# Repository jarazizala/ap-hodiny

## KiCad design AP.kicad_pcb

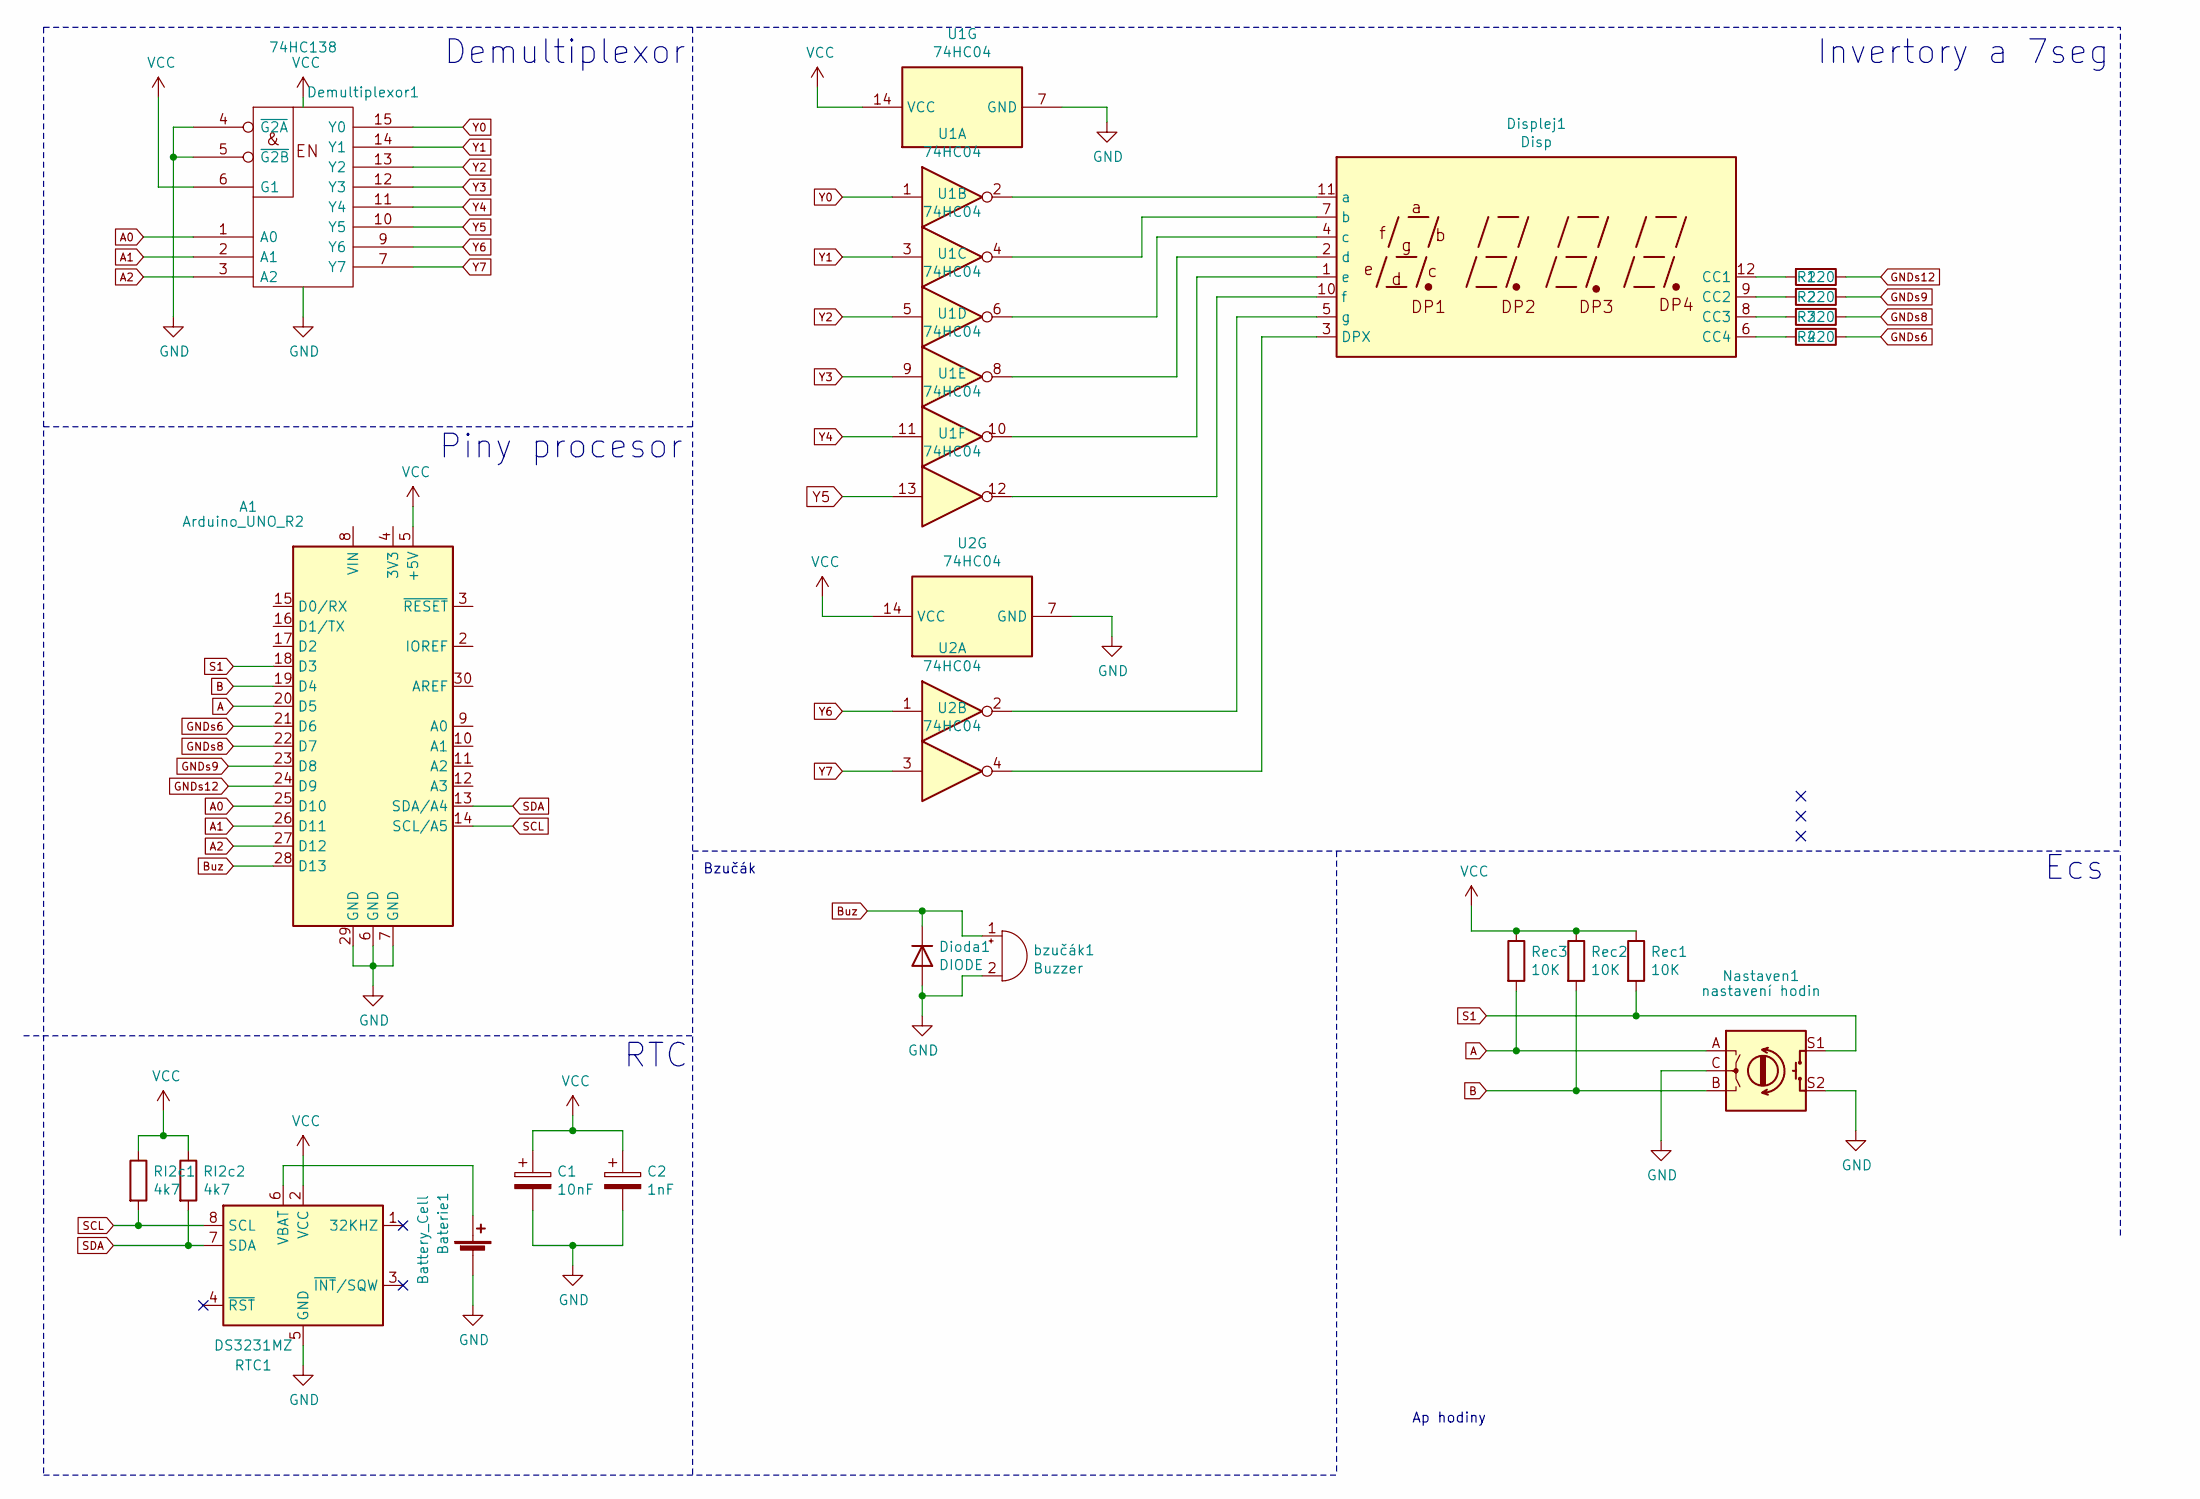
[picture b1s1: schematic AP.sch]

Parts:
A1: Arduino_UNO_R2
Baterie1: Battery_Cell; BatteryHolder_Keystone_1060_1x2032
C1: 10nF; C_0805_2012Metric
C2: 1nF; C_0805_2012Metric
Demultiplexor1: 74HC138; SO-16_3.9x9.9mm_P1.27mm
Dioda1: DIODE; D_SMA
Displej1: Disp; CA56-12SRWA
Nastaven1: nastavení hodin; RotaryEncoder_Alps_EC11E-Switch_Vertical_H20mm
R1, R2, R3, R4: 220; R_0805_2012Metric
RI2c1, RI2c2: 4k7; R_0805_2012Metric
RTC1: DS3231MZ; SO-8_3.9x4.9mm_P1.27mm
Rec1, Rec2, Rec3: 10K; R_0805_2012Metric
U1, U2: 74HC04; SO-14_3.9x8.65mm_P1.27mm
bzučák1: Buzzer; Buzzer_12x9.5RM7.6

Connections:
A: A1.20 (D5), Nastaven1.A, Rec3.2
A0: A1.25 (D10), Demultiplexor1.1 (A0)
A1: A1.26 (D11), Demultiplexor1.2 (A1)
A2: A1.27 (D12), Demultiplexor1.3 (A2)
B: A1.19 (D4), Nastaven1.B, Rec2.2
Buz: A1.28 (D13), Dioda1.2 (K), bzučák1.1 (-)
GND: A1.6 (GND), A1.7 (GND), A1.29 (GND), Baterie1.2 (-), C1.2, C2.2, Demultiplexor1.4 (~G2A), Demultiplexor1.5 (~G2B), Demultiplexor1.8 (GND), Dioda1.1 (A), Nastaven1.C, Nastaven1.S2, RTC1.5 (GND), U1.7 (GND), U2.7 (GND), bzučák1.2 (+)
GNDs6: A1.21 (D6), R4.1
GNDs8: A1.22 (D7), R3.1
GNDs9: A1.23 (D8), R2.1
GNDs12: A1.24 (D9), R1.1
unnamed: Baterie1.1 (+), RTC1.6 (VBAT)
unnamed: Displej1.1 (e), U1.10
unnamed: Displej1.2 (d), U1.8
unnamed: Displej1.3 (DPX), U2.4
unnamed: Displej1.4 (c), U1.6
unnamed: Displej1.5 (g), U2.2
unnamed: Displej1.6 (CC4), R4.2
unnamed: Displej1.7 (b), U1.4
unnamed: Displej1.8 (CC3), R3.2
unnamed: Displej1.9 (CC2), R2.2
unnamed: Displej1.10 (f), U1.12
unnamed: Displej1.11 (a), U1.2
unnamed: Displej1.12 (CC1), R1.2
S1: A1.18 (D3), Nastaven1.S1, Rec1.2
SCL: A1.14 (SCL/A5), RI2c1.2, RTC1.8 (SCL)
SDA: A1.13 (SDA/A4), RI2c2.2, RTC1.7 (SDA)
VCC: A1.5 (+5V), C1.1, C2.1, Demultiplexor1.6 (G1), Demultiplexor1.16 (VCC), RI2c1.1, RI2c2.1, RTC1.2 (VCC), Rec1.1, Rec2.1, Rec3.1, U1.14 (VCC), U2.14 (VCC)
Y0: Demultiplexor1.15 (Y0), U1.1
Y1: Demultiplexor1.14 (Y1), U1.3
Y2: Demultiplexor1.13 (Y2), U1.5
Y3: Demultiplexor1.12 (Y3), U1.9
Y4: Demultiplexor1.11 (Y4), U1.11
Y5: Demultiplexor1.10 (Y5), U1.13
Y6: Demultiplexor1.9 (Y6), U2.1
Y7: Demultiplexor1.7 (Y7), U2.3

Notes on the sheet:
Ap hodiny
RTC
Demultiplexor
Invertory a 7seg
Piny procesor
Ecs
Bzučák

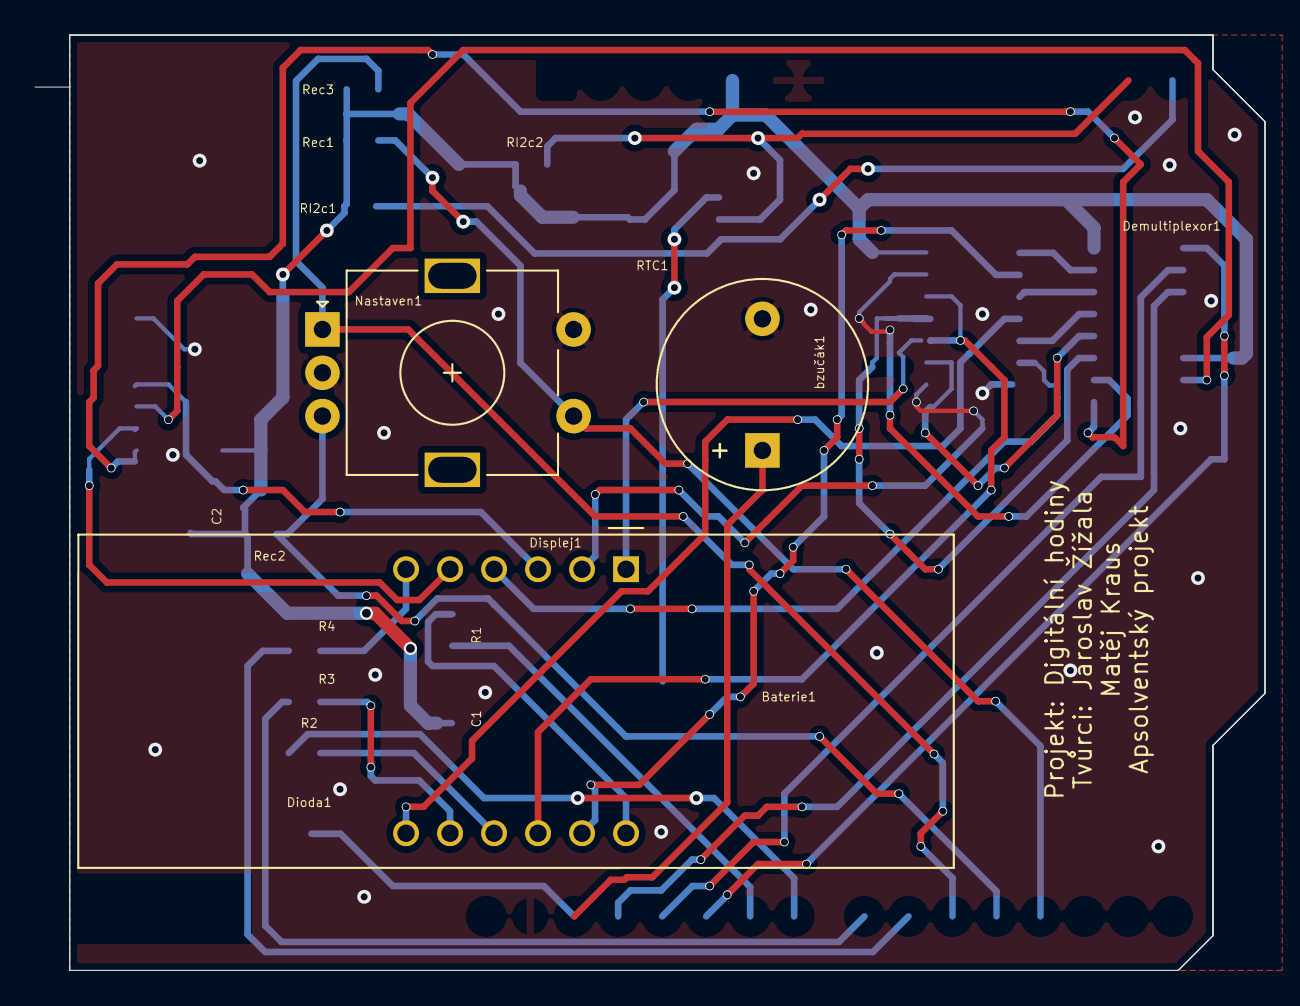
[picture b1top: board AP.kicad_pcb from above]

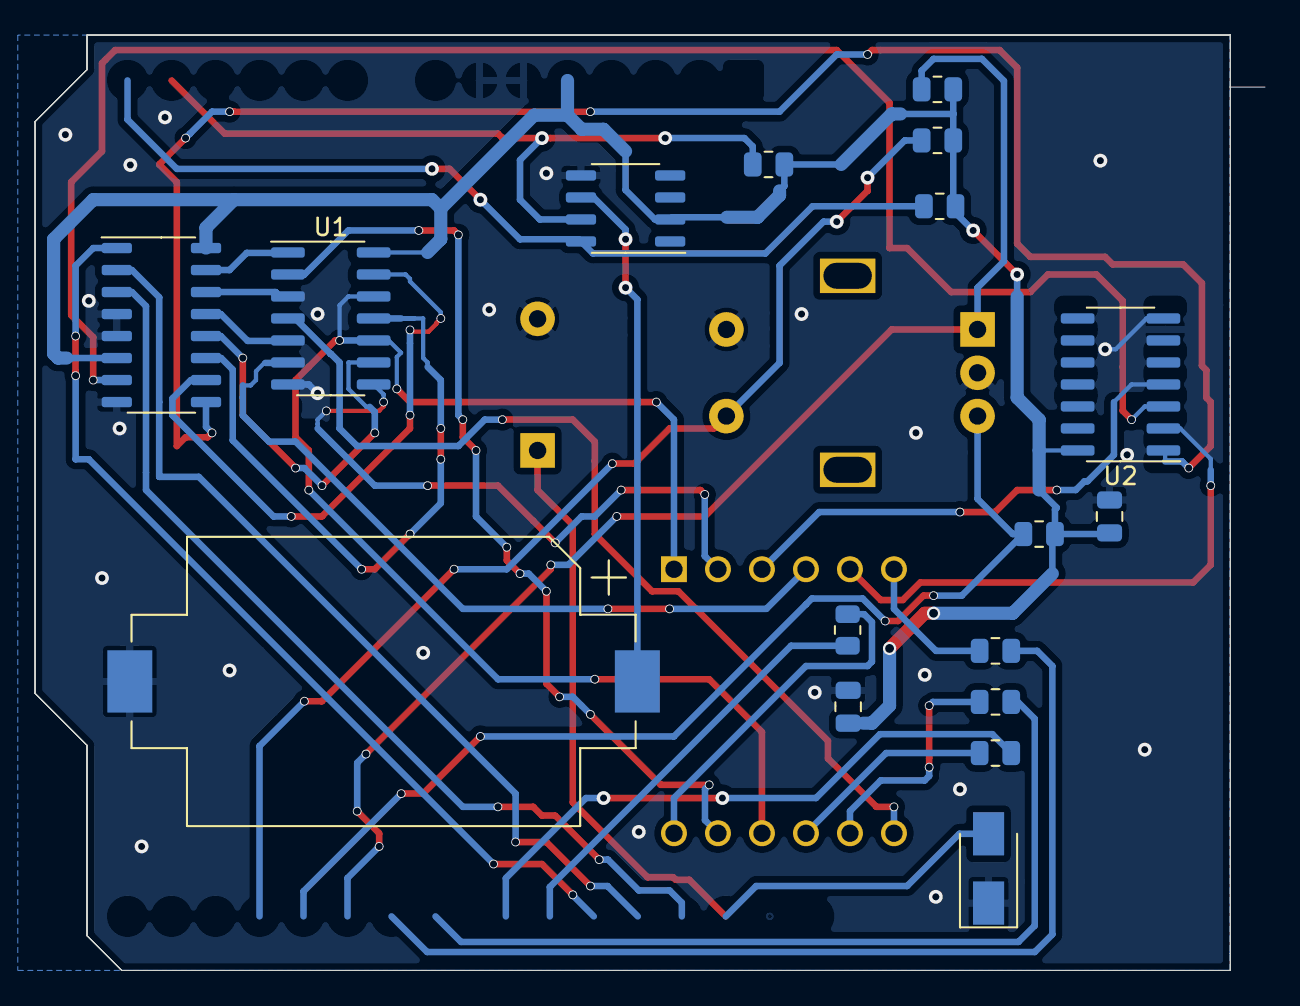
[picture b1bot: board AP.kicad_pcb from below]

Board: 2 copper layers, 71.0 x 54.0 mm, 20 parts (17 on the bottom side), 29 nets.

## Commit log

2021-01-12 test
2021-01-14 start
2021-01-14 start2
2021-01-22 finále
2021-01-27 posledni_oprava
2021-03-13 1
    1
